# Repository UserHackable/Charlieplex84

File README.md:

## Charlieplex84 

### Board dimensions

* (270000, 275000) original units
* (2.7000, 2.7500) inches
* (68.5800, 69.8500) mm

| Front | Back |
| --- | --- |
|  |  |

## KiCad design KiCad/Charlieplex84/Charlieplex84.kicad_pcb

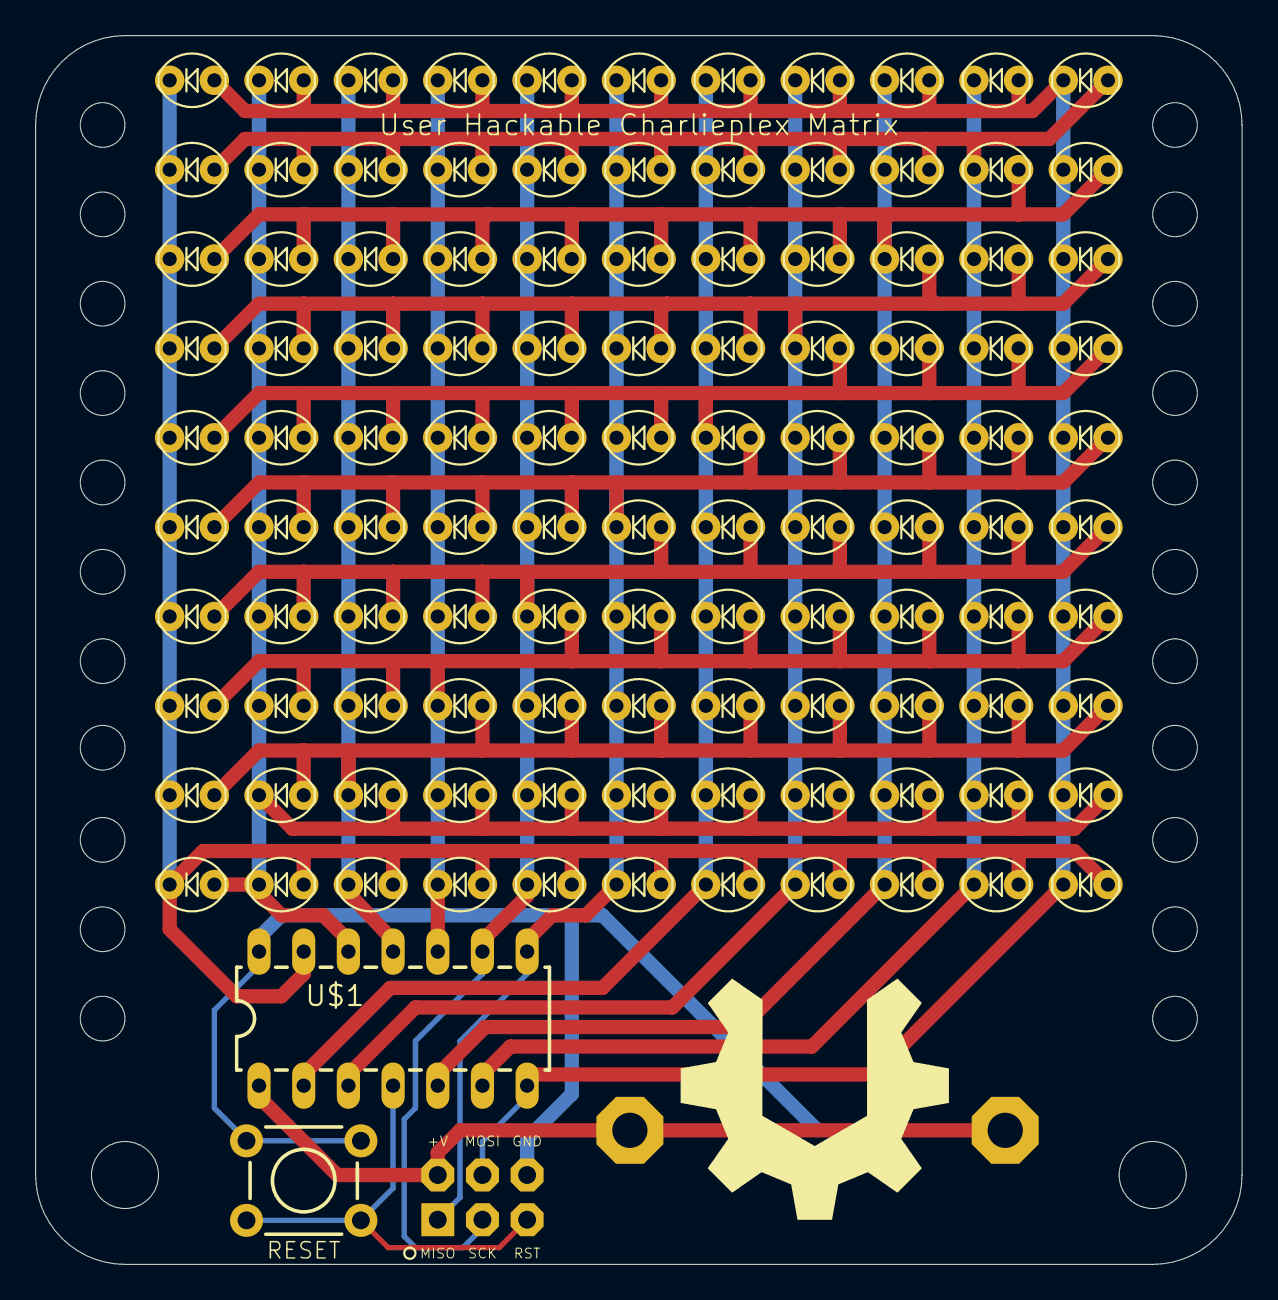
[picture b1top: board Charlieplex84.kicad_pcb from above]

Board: 2 copper layers, 68.6 x 69.8 mm, 139 parts (1 on the bottom side), 14 nets.

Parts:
J1: ICSP; 2X3-NS
LED_0_1, LED_0_2, LED_0_3, LED_0_4, LED_0_5, LED_0_6, LED_0_7, LED_0_8, LED_0_9, LED_0_10, LED_1_0, LED_1_2, LED_1_3, LED_1_4, LED_1_5, LED_1_6, LED_1_7, LED_1_8, LED_1_9, LED_1_10, LED_2_0, LED_2_1, LED_2_3, LED_2_4, LED_2_5, LED_2_6, LED_2_7, LED_2_8, LED_2_9, LED_2_10, LED_3_0, LED_3_1, LED_3_2, LED_3_4, LED_3_5, LED_3_6, LED_3_7, LED_3_8, LED_3_9, LED_3_10, LED_4_0, LED_4_1, LED_4_2, LED_4_3, LED_4_5, LED_4_6, LED_4_7, LED_4_8, LED_4_9, LED_4_10, LED_5_0, LED_5_1, LED_5_2, LED_5_3, LED_5_4, LED_5_6, LED_5_7, LED_5_8, LED_5_9, LED_5_10, LED_6_0, LED_6_1, LED_6_2, LED_6_3, LED_6_4, LED_6_5, LED_6_7, LED_6_8, LED_6_9, LED_6_10, LED_7_0, LED_7_1, LED_7_2, LED_7_3, LED_7_4, LED_7_5, LED_7_6, LED_7_8, LED_7_9, LED_7_10, LED_8_0, LED_8_1, LED_8_2, LED_8_3, LED_8_4, LED_8_5, LED_8_6, LED_8_7, LED_8_9, LED_8_10, LED_9_0, LED_9_1, LED_9_2, LED_9_3, LED_9_4, LED_9_5, LED_9_6, LED_9_7, LED_9_8, LED_9_10, LED_10_0, LED_10_1, LED_10_2, LED_10_3, LED_10_4, LED_10_5, LED_10_6, LED_10_7, LED_10_8, LED_10_9: LED-OVAL
S1: TACTILE-PTH
U$1: ATTINY84; DIL14
U$2: CR2032-THRU
U$3: USER_HACKABLE
UNK_HOLE_0: dummyfp0
UNK_HOLE_1: dummyfp1
UNK_HOLE_2: dummyfp2
UNK_HOLE_3: dummyfp3
UNK_HOLE_4: dummyfp4
UNK_HOLE_5: dummyfp5
UNK_HOLE_6: dummyfp6
UNK_HOLE_7: dummyfp7
UNK_HOLE_8: dummyfp8
UNK_HOLE_9: dummyfp9
UNK_HOLE_10: dummyfp10
UNK_HOLE_11: dummyfp11
UNK_HOLE_12: dummyfp12
UNK_HOLE_13: dummyfp13
UNK_HOLE_14: dummyfp14
UNK_HOLE_15: dummyfp15
UNK_HOLE_16: dummyfp16
UNK_HOLE_17: dummyfp17
UNK_HOLE_18: dummyfp18
UNK_HOLE_19: dummyfp19
UNK_HOLE_20: dummyfp20
UNK_HOLE_21: dummyfp21
UNK_HOLE_22: dummyfp22
UNK_HOLE_23: dummyfp23

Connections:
5V: J1.2, U$1.1, U$2.+1, U$2.+2
GND: J1.6, S1.1, S1.2, U$1.14, U$2.-
P0: LED_0_1.CATHODE, LED_0_2.CATHODE, LED_0_3.CATHODE, LED_0_4.CATHODE, LED_0_5.CATHODE, LED_0_6.CATHODE, LED_0_7.CATHODE, LED_0_8.CATHODE, LED_0_9.CATHODE, LED_0_10.CATHODE, LED_1_0.ANODE, LED_2_0.ANODE, LED_3_0.ANODE, LED_4_0.ANODE, LED_5_0.ANODE, LED_6_0.ANODE, LED_7_0.ANODE, LED_8_0.ANODE, LED_9_0.ANODE, LED_10_0.ANODE, U$1.13
P1: LED_0_1.ANODE, LED_1_0.CATHODE, LED_1_2.CATHODE, LED_1_3.CATHODE, LED_1_4.CATHODE, LED_1_5.CATHODE, LED_1_6.CATHODE, LED_1_7.CATHODE, LED_1_8.CATHODE, LED_1_9.CATHODE, LED_1_10.CATHODE, LED_2_1.ANODE, LED_3_1.ANODE, LED_4_1.ANODE, LED_5_1.ANODE, LED_6_1.ANODE, LED_7_1.ANODE, LED_8_1.ANODE, LED_9_1.ANODE, LED_10_1.ANODE, U$1.12
P2: LED_0_2.ANODE, LED_1_2.ANODE, LED_2_0.CATHODE, LED_2_1.CATHODE, LED_2_3.CATHODE, LED_2_4.CATHODE, LED_2_5.CATHODE, LED_2_6.CATHODE, LED_2_7.CATHODE, LED_2_8.CATHODE, LED_2_9.CATHODE, LED_2_10.CATHODE, LED_3_2.ANODE, LED_4_2.ANODE, LED_5_2.ANODE, LED_6_2.ANODE, LED_7_2.ANODE, LED_8_2.ANODE, LED_9_2.ANODE, LED_10_2.ANODE, U$1.11
P3: LED_0_3.ANODE, LED_1_3.ANODE, LED_2_3.ANODE, LED_3_0.CATHODE, LED_3_1.CATHODE, LED_3_2.CATHODE, LED_3_4.CATHODE, LED_3_5.CATHODE, LED_3_6.CATHODE, LED_3_7.CATHODE, LED_3_8.CATHODE, LED_3_9.CATHODE, LED_3_10.CATHODE, LED_4_3.ANODE, LED_5_3.ANODE, LED_6_3.ANODE, LED_7_3.ANODE, LED_8_3.ANODE, LED_9_3.ANODE, LED_10_3.ANODE, U$1.10
P4: J1.3, LED_0_4.ANODE, LED_1_4.ANODE, LED_2_4.ANODE, LED_3_4.ANODE, LED_4_0.CATHODE, LED_4_1.CATHODE, LED_4_2.CATHODE, LED_4_3.CATHODE, LED_4_5.CATHODE, LED_4_6.CATHODE, LED_4_7.CATHODE, LED_4_8.CATHODE, LED_4_9.CATHODE, LED_4_10.CATHODE, LED_5_4.ANODE, LED_6_4.ANODE, LED_7_4.ANODE, LED_8_4.ANODE, LED_9_4.ANODE, LED_10_4.ANODE, U$1.9
P5: J1.1, LED_0_5.ANODE, LED_1_5.ANODE, LED_2_5.ANODE, LED_3_5.ANODE, LED_4_5.ANODE, LED_5_0.CATHODE, LED_5_1.CATHODE, LED_5_2.CATHODE, LED_5_3.CATHODE, LED_5_4.CATHODE, LED_5_6.CATHODE, LED_5_7.CATHODE, LED_5_8.CATHODE, LED_5_9.CATHODE, LED_5_10.CATHODE, LED_6_5.ANODE, LED_7_5.ANODE, LED_8_5.ANODE, LED_9_5.ANODE, LED_10_5.ANODE, U$1.8
P6: LED_0_6.ANODE, LED_1_6.ANODE, LED_2_6.ANODE, LED_3_6.ANODE, LED_4_6.ANODE, LED_5_6.ANODE, LED_6_0.CATHODE, LED_6_1.CATHODE, LED_6_2.CATHODE, LED_6_3.CATHODE, LED_6_4.CATHODE, LED_6_5.CATHODE, LED_6_7.CATHODE, LED_6_8.CATHODE, LED_6_9.CATHODE, LED_6_10.CATHODE, LED_7_6.ANODE, LED_8_6.ANODE, LED_9_6.ANODE, LED_10_6.ANODE, U$1.2
P7: LED_0_7.ANODE, LED_1_7.ANODE, LED_2_7.ANODE, LED_3_7.ANODE, LED_4_7.ANODE, LED_5_7.ANODE, LED_6_7.ANODE, LED_7_0.CATHODE, LED_7_1.CATHODE, LED_7_2.CATHODE, LED_7_3.CATHODE, LED_7_4.CATHODE, LED_7_5.CATHODE, LED_7_6.CATHODE, LED_7_8.CATHODE, LED_7_9.CATHODE, LED_7_10.CATHODE, LED_8_7.ANODE, LED_9_7.ANODE, LED_10_7.ANODE, U$1.3
P8: LED_0_8.ANODE, LED_1_8.ANODE, LED_2_8.ANODE, LED_3_8.ANODE, LED_4_8.ANODE, LED_5_8.ANODE, LED_6_8.ANODE, LED_7_8.ANODE, LED_8_0.CATHODE, LED_8_1.CATHODE, LED_8_2.CATHODE, LED_8_3.CATHODE, LED_8_4.CATHODE, LED_8_5.CATHODE, LED_8_6.CATHODE, LED_8_7.CATHODE, LED_8_9.CATHODE, LED_8_10.CATHODE, LED_9_8.ANODE, LED_10_8.ANODE, U$1.5
P9: LED_0_9.ANODE, LED_1_9.ANODE, LED_2_9.ANODE, LED_3_9.ANODE, LED_4_9.ANODE, LED_5_9.ANODE, LED_6_9.ANODE, LED_7_9.ANODE, LED_8_9.ANODE, LED_9_0.CATHODE, LED_9_1.CATHODE, LED_9_2.CATHODE, LED_9_3.CATHODE, LED_9_4.CATHODE, LED_9_5.CATHODE, LED_9_6.CATHODE, LED_9_7.CATHODE, LED_9_8.CATHODE, LED_9_10.CATHODE, LED_10_9.ANODE, U$1.6
P10: J1.4, LED_0_10.ANODE, LED_1_10.ANODE, LED_2_10.ANODE, LED_3_10.ANODE, LED_4_10.ANODE, LED_5_10.ANODE, LED_6_10.ANODE, LED_7_10.ANODE, LED_8_10.ANODE, LED_9_10.ANODE, LED_10_0.CATHODE, LED_10_1.CATHODE, LED_10_2.CATHODE, LED_10_3.CATHODE, LED_10_4.CATHODE, LED_10_5.CATHODE, LED_10_6.CATHODE, LED_10_7.CATHODE, LED_10_8.CATHODE, LED_10_9.CATHODE, U$1.7
RST: J1.5, S1.3, S1.4, U$1.4

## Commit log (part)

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2016-04-07 updating files
2016-04-07 updating battery
2016-04-07 from Makefile
